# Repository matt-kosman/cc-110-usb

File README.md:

# cc-110-usb

The cc-110-usb converter allows you to connect a ClearCom [CC-110](https://www.clearcom.com/product/cc-110/) single-ear headset to a computer or smartphone via class-compliant USB audio.

<p align="center"></br><b>cc-110-usb without enclosure</b></p>

# build

Build a cc-110-usb using the included design files:
* Order a set of 3 PCBs from [OSHPark](https://oshpark.com/shared_projects/4OjzXrBn) or send the [gerbers](build/cc-110-usb_gerber.zip) to your preferred supplier. This project involves surface mount soldering in a small space. Review the PCB layout before proceeding.
* Import the [BOM](build/cc-110-usb_bom.csv) directly into Mouser, parse it with your favorite BOM tool, or order parts individually.
* Assemble the PCB according to the [schematic](build/cc-110-usb_schematic.pdf).
* Print the enclosure from the [STLs](enclosure/) or order from a 3D-printing service. You will also need suitable hardware and tools, described in the enclosure section.

Estimated cost for one unit at the time of writing is less than 25 USD, excluding tax, shipping, and consumables.

# narrative

As I needed to carry a CC-110 headset for work, I started this project so that I could also use it with my computer. The CC-110 has significantly better noise rejection than my laptop microphone and helps when speaking in a loud environment. I do not recommend buying a CC-110 just to use with this converter, since there are many headsets that will work without a converter or offer better quality with less effort.

At the time of writing, I have used the cc-110-usb for about a year with excellent results. I have no way to quantify the performance, but I can report a meaningful reduction in background noise compared to my laptop microphone and positive comments from peers about sound quality.

# electrical design

## cc-110 specifications

The CC-110 has the following relevant electrical specifications, which have been extracted from its product page. All values are typical and measured at 1 kHz.
* **Speaker Impedance** 400 ±30% Ohms
* **Microphone Impedance** 200 ±30% Ohms
* **Open Circuit Sensitivity** -64 ±3.5 dB V at 99 dB ±3 dB SPL
* **Connector** 4-Pin XLR, Female (XLR4F), with pinout below

<br/>

XLR4F Pin | Function
------ | ----
1 | `MIC -`
2 | `MIC +`
3 | `SPK -`
4 | `SPK +`

<br/>

A typical conversation causes approximately [60 dB SPL](https://www.cdc.gov/nceh/hearing_loss/what_noises_cause_hearing_loss.html). Assuming a 2 m distance, 1 cm microphone placement, and that sound pressure decreases at *1/r*, a typical human might output 106 db SPL at the microphone, which calculates to **4 mVpp** at the microphone connector.

No sensitivity is given for the headphone. The compatible ClearCom [HMS-4X](https://www.clearcom.com/product/hms-4x/) provides up to 3.1 V (+12 dB uV) output. The minimum headphone impedance of 32 Ohms suggests an internal resistance of approximately the same. Therefore, the power delivered to the headphones is around **20 mW**. At a [representative sensitivity](https://service.shure.com/s/article/understanding-earphone-headphone-specifications?language=en_US) of 100 dB SPL / mW, the headphone would produce 113 dB SPL. This is a loud but believable output, considering the HMS-4X can drive multiple headsets in parallel and that the system is designed to work in noisy environments.

There are a lot of assumptions here, but the results should reasonably inform the requirements for amplifier, ADC, and DAC performance.

## audio codec

The Texas Instruments [PCM2912A](https://www.ti.com/lit/ds/symlink/pcm2912a.pdf) (PDF) is a USB class-class compliant audio codec with integrated stereo DAC and mono ADC. It is well suited to this application.

The PCM2912A provides a 20 kOhm microphone preamplifier with fixed 20 dB gain followed by up to 30 dB of USB-programmable gain. The PCM2912A ADC accepts **1.4 Vpp** before clipping. The estimated input voltage of 4 mVpp after 50dB of gain is **1.3 Vpp** and should therefore be a reasonable match for the ADC.

The PCM2912A provides a maximum per-channel speaker output of 1.3 V, yielding 13 mW into a 32 Ohm load from a calculated 32 Ohm internal resistance. Connecting the CC-110 400 Ohm load and summing the left and right channels through a comparably low value mixing resistor results in about **14 mW** delivered to the headset. This is less than the estimated HMS-4X maximum output but still sufficient to produce 110 dB SPL from the representative earpiece. The actual output volume will also depend on the level of the media source and the USB-programmable attenuation.

# pcb design

## components
Components were selected, in priority order,
1. To meet the requirements of the circuit;
1. To be possible to hand solder with an iron;
1. To source from a single supplier (at the time of design); and
1. To minimize cost.

USB C allows the converter to easily connect to both laptops and smartphones. It is easily adapted to USB A externally if required.

<p align="center"></br><b>CC-110 PCB top</b></p>

## layout
Layout is primarily optimized for size, with locations assigned based on trace length sensitivity.

Decoupling capacitors are placed beneath the PCM2912A IC; the microphone input trace is short and separated from other traces. To the extent possible, analog signals and digital signals are separated on opposite sides of the board, though they share the same ground plane.

<p align="center"></br><b>CC-110 PCB bottom</b></p>

Other common layout best practices have a negligible impact due to the small PCB size and are therefore deprioritized. For example, the crystal and IC are located on opposite sides of the board, but the absolute length is still small enough to prevent the need to specifically tune the load capacitors. Similarly, the USB traces leave the connector from both sides, rather than in parallel, but the short distance mitigates signal loss or noise issues.

# mechanical design

<p align="center"></br><b>cc-110-usb in enclosure</b></p>

A basic 3D-printed cylindrical enclosure contains the cc-110-usb PCB assembly. The mechanical design is primarily functional, with no specific assessment of durability or stress.

The enclosure is constructed of two parts. A single machine screw restrains the XLR4-side enclosure, the XLR4 connector itself, and the USB-side enclosure. The USB-side enclosure has a standoff that captures a retaining nut and a slot to hold the PCB.

<p align="center"></br><b>cc-110-usb enclosure disassembled</b></p>

The pictured assembly uses a McMaster [92949A116](https://www.mcmaster.com/92949A116/) machine screw and [91841A005](https://www.mcmaster.com/91841A005/) nut. This \#4-40 screw is slightly too large for the XLR4 connector's opening, and a small file was used to increase the diameter of the XLR4. A smaller screw may avoid this problem.

Similarly, depending on the quality of 3D print, the USB-side enclosure may need some filing for the PCB to sit flush in the slot.

# history

Before designing the USB converter, I first attempted a direct connection from the XLR4 to my laptop's TRRS headset jack.

<p align="center"></br><b>passive XLR4 to TRRS adapter</b></p>

While this worked with my phone, it did not work with my laptop. Further research then suggested that a passive converter is not the right approach because performance would vary across devices.
* Each device has unique gain capabilities and microphone impedance requirements, which can affect the ability to cleanly amplify a signal from the CC-110.
* Many devices sense the resistance between `MIC +` and `GND` to detect the presence of a microphone or the activation of an in-line control. The impedance levels are [well-understood](https://source.android.com/devices/accessories/headset/plug-headset-spec) but possibly incompatible with the CC-110's 200 Ohms, depending on the individual implementation. An impedance transformer or terminator would be required for compatibility, further complicating the gain considerations above.
* Some devices apply as bias voltage to detect the presence of in-line controls or to power an electret-style microphone. Bias is not necessary for the CC-110's dynamic microphone and may cause damage.

# changelog

## breadboard
The breadboard implementation performs well, and validates the assumptions enough to proceed to a PCB design. Some noise is audible, but it seems to be related to poor grounding. A proper ground plane on the PCB should reduce the noise. Microphone levels are acceptable at gains between 50% and 100%, depending on speaking volume and microphone placement. Speaker output is loud enough within the range of 20% to 50%, depending on source level.

## REV A
Noise improved as expected and is no longer an issue. Overall performance matched expectations.

# license
The cc-110-usb is licensed under [CC BY-NC-SA 4.0](https://creativecommons.org/licenses/by-nc-sa/4.0/).

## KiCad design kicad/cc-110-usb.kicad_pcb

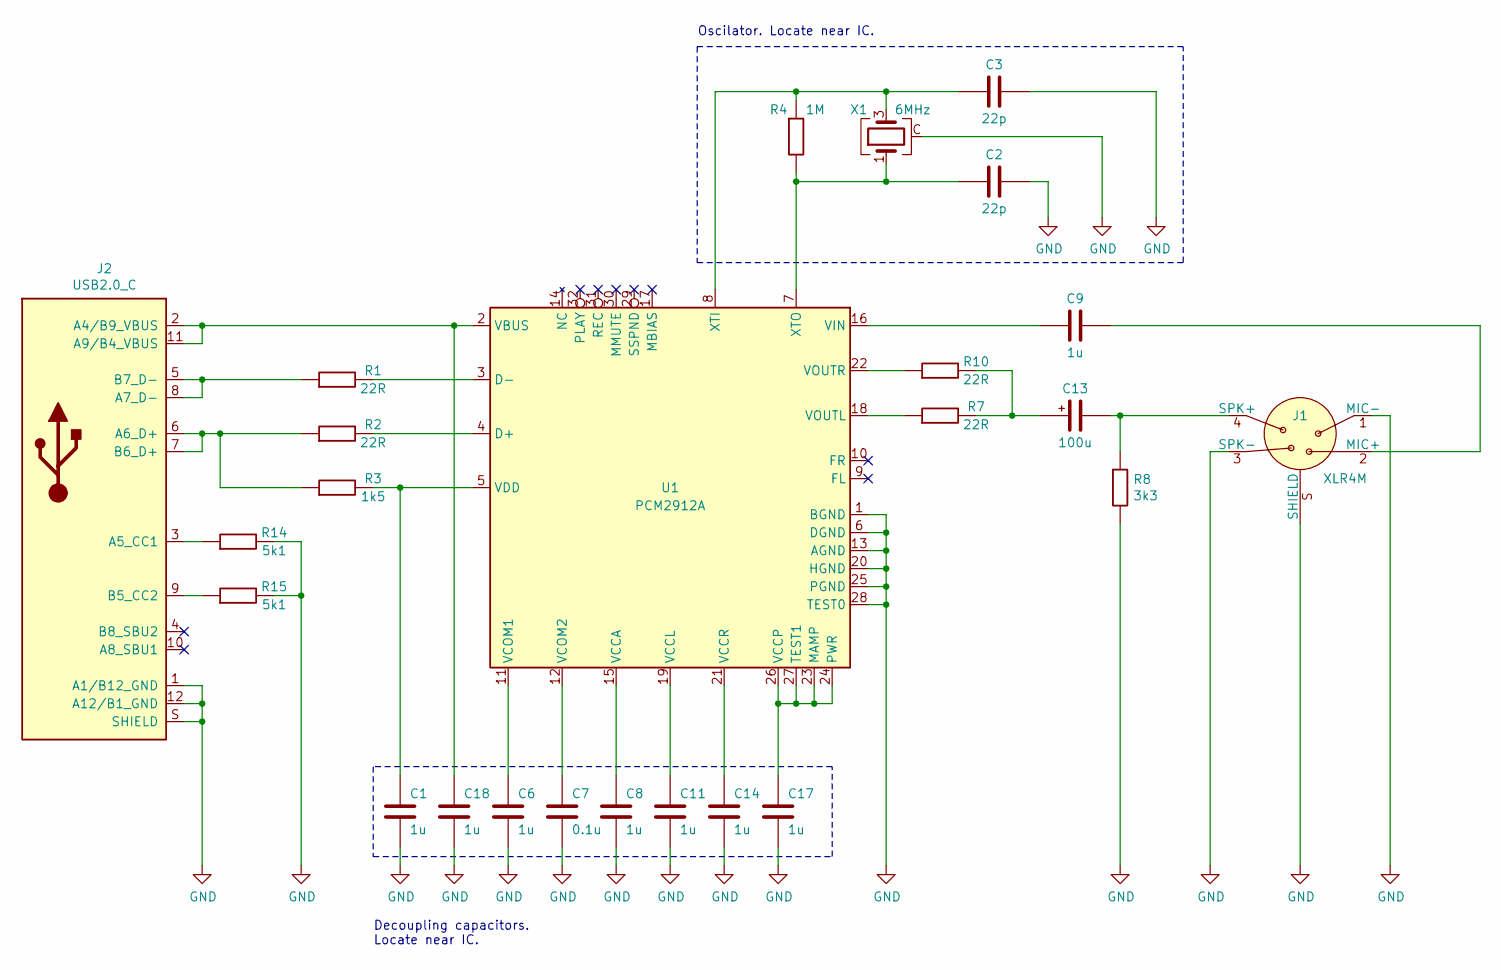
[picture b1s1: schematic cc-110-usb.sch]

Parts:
C1, C6, C8, C9, C11, C14, C17, C18: 1u; C_0603_0.9mm; MPN CL10B105MO8NNWC; Mouser 187-CL10B105MO8NNWC
C2, C3: 22p; C_0603_0.9mm; MPN CL10C220JB8NNNC; Mouser 187-CL10C220JB8NNNC
C7: 0.1u; C_0603_0.9mm; MPN CL10B104KO8NNNC; Mouser 187-CL10B104KO8NNNC
C13: 100u; C_6.3x7.7mm; MPN UWT1V101MCL1GS; Mouser 647-UWT1V101MCL1S
J1: XLR4M; J_NC4MAH; MPN NC4MAH; Mouser 568-NC4MAH
J2: USB2.0_C; J_DX07S016JA1R1500; MPN DX07S016JA1R1500; Mouser 656-DX07S016JA1R1500
R1, R2, R7, R10: 22R; R_0603_0.5mm; MPN MCT06030C2209FP500; Mouser 594-MCT06030C2209FP5
R3: 1k5; R_0603_0.5mm; MPN MCT06030C1501FP500; Mouser 594-MCT06030C1501FP5
R4: 1M; R_0603_0.5mm; MPN MCT06030C1004FP500; Mouser 594-MCT06030C1004FP5
R8: 3k3; R_0603_0.5mm; MPN MCT06030C3301FP500; Mouser 594-MCT06030C3301FP5
R14, R15: 5k1; R_0603_0.5mm; MPN MCT06030C5101FP500; Mouser 594-MCT06030C5101FP5
U1: PCM2912A; U_TQFP-32_7x7mm_P0.8mm; MPN PCM2912APJTR; Mouser 595-PCM2912APJTR
X1: 6MHz; X_7050_1.3mm; MPN ABMM-6.000MHZ-B2-T; Mouser 815-ABMM-6-B2-T

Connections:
GND: C1.2, C2.2, C3.2, C6.2, C7.2, C8.2, C11.2, C14.2, C17.2, C18.2, J1.1 (MIC-), J1.3 (SPK-), J1.S (SHIELD), J2.1 (A1/B12_GND), J2.12 (A12/B1_GND), J2.S (SHIELD), R8.2, R14.2, R15.2, U1.1 (BGND), U1.6 (DGND), U1.13 (AGND), U1.20 (HGND), U1.25 (PGND), U1.28 (TEST0), X1.C
unnamed: C1.1, R3.2, U1.5 (VDD)
unnamed: C2.1, R4.2, U1.7 (XTO), X1.1
unnamed: C3.1, R4.1, U1.8 (XTI), X1.3
unnamed: C6.1, U1.11 (VCOM1)
unnamed: C7.1, U1.12 (VCOM2)
unnamed: C8.1, U1.15 (VCCA)
unnamed: C9.1, U1.16 (VIN)
unnamed: C9.2, J1.2 (MIC+)
unnamed: C11.1, U1.19 (VCCL)
unnamed: C13.1, R7.2, R10.2
unnamed: C13.2, J1.4 (SPK+), R8.1
unnamed: C14.1, U1.21 (VCCR)
unnamed: C17.1, U1.23 (MAMP), U1.24 (PWR), U1.26 (VCCP), U1.27 (TEST1)
unnamed: C18.1, J2.2 (A4/B9_VBUS), J2.11 (A9/B4_VBUS), U1.2 (VBUS)
unnamed: J2.3 (A5_CC1), R14.1
unnamed: J2.5 (B7_D-), J2.8 (A7_D-), R1.1
unnamed: J2.6 (A6_D+), J2.7 (B6_D+), R2.1, R3.1
unnamed: J2.9 (B5_CC2), R15.1
unnamed: R1.2, U1.3 (D-)
unnamed: R2.2, U1.4 (D+)
unnamed: R7.1, U1.18 (VOUTL)
unnamed: R10.1, U1.22 (VOUTR)

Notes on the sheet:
Decoupling capacitors. Locate near IC.
Oscilator. Locate near IC.

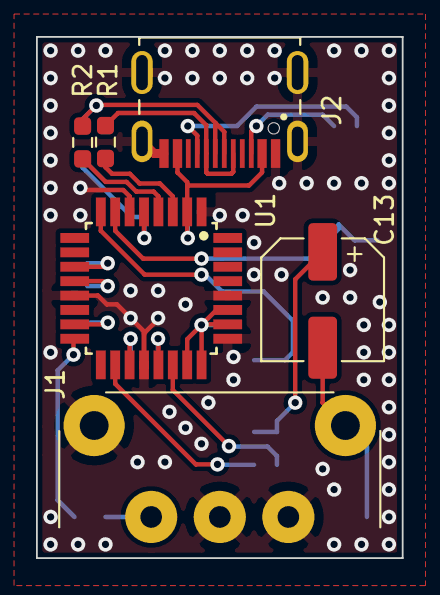
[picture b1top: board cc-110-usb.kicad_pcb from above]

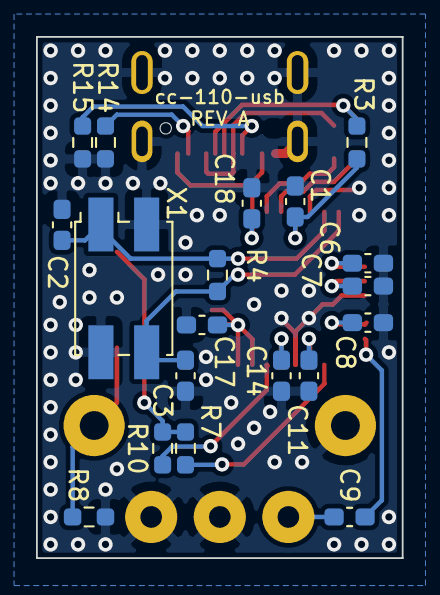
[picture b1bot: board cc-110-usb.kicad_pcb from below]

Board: 2 copper layers, 20.3 x 29.0 mm, 25 parts (19 on the bottom side), 23 nets.

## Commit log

2020-11-29 breadboard
    Documented design theory and results of breadboard test. Added license.
2020-12-03 Created KiCAD Project
2020-12-03 Added resistors and capacitors to project library
2020-12-07 Added PCM2912 and crystal, updated formatting
2020-12-08 Added USB C connector and pull down resistor
2020-12-09 Added XLR4M connector
2020-12-11 Schematic capture
2020-12-15 Added PCB
2020-12-16 Added schematic, BOM, and gerber
2020-12-18 Gerber review and readme update
2021-12-07 Added images
2021-12-07 Added enclosure STLs
2021-12-07 Add title to README
2021-12-07 Update .gitignore to include .csv files for BOM
2021-12-07 Update README to fix images
